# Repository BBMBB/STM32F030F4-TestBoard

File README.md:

# STM32F030F4-TestBoard

## Summary

Simple breadbord compatible testboard based on the STM32F030F4.
I created this pcb to test various applications with the STM32F030F4.
The SWD-Port is accessable through a seperate pinheader for programming.

## Screenshots

## BOM

| **Designator** | **Quantity** | **Value**   | **LCSC** |
|----------------|--------------|-------------|----------|
| C1, C2         | 2            | 10 uF       | C72487   |
| C7, C8, C11    | 3            | 100 nF      | C110253  |
| C9, C10        | 2            | 1 uF        | C1848    |
| R5             | 1            | 0 Ohm       | C100045  |
| U1             | 1            | LM1117-3.3  | C126027  |
| U2             | 1            | STM32F030F4 | C89040   |

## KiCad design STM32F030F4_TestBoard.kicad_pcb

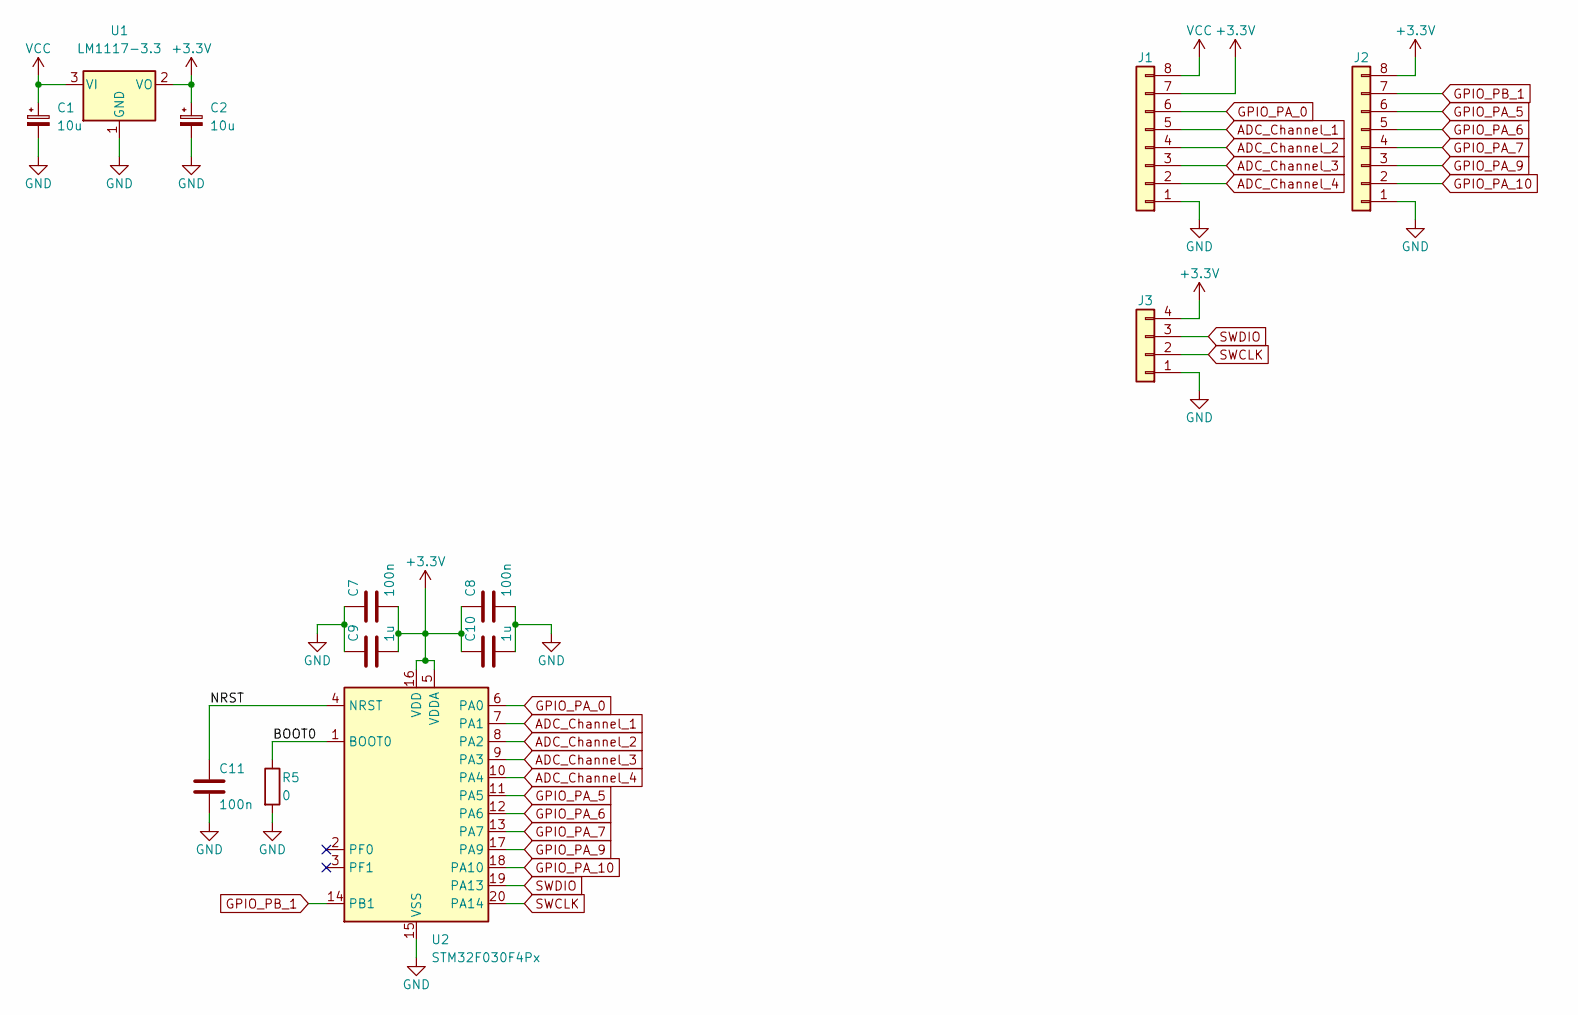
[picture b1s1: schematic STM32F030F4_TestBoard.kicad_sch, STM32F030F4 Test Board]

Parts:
C1, C2: 10u; CP_Elec_5x5.4; LCSC C72487
C7, C8, C11: 100n; C_1206_3216Metric; LCSC C110253
C9, C10: 1u; C_1206_3216Metric; LCSC C1848
J1, J2: Conn_01x08; PinHeader_1x08_P2.54mm_Vertical
J3: Conn_01x04; PinHeader_1x04_P2.54mm_Vertical
R5: 0; R_0805_2012Metric; LCSC C100045
U1: LM1117-3.3; SOT-223-3_TabPin2; LCSC C126027
U2: STM32F030F4Px; TSSOP-20_4.4x6.5mm_P0.65mm

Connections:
+3V3: C2.1, C7.2, C8.1, C9.2, C10.1, J1.7, J2.8, J3.4, U1.2 (VO), U2.5 (VDDA), U2.16 (VDD)
/BOOT0: R5.1, U2.1 (BOOT0)
/NRST: C11.1, U2.4 (NRST)
ADC_Channel_1: J1.5, U2.7 (PA1)
ADC_Channel_2: J1.4, U2.8 (PA2)
ADC_Channel_3: J1.3, U2.9 (PA3)
ADC_Channel_4: J1.2, U2.10 (PA4)
GND: C1.2, C2.2, C7.1, C8.2, C9.1, C10.2, C11.2, J1.1, J2.1, J3.1, R5.2, U1.1 (GND), U2.15 (VSS)
GPIO_PA_0: J1.6, U2.6 (PA0)
GPIO_PA_5: J2.6, U2.11 (PA5)
GPIO_PA_6: J2.5, U2.12 (PA6)
GPIO_PA_7: J2.4, U2.13 (PA7)
GPIO_PA_9: J2.3, U2.17 (PA9)
GPIO_PA_10: J2.2, U2.18 (PA10)
GPIO_PB_1: J2.7, U2.14 (PB1)
SWCLK: J3.2, U2.20 (PA14)
SWDIO: J3.3, U2.19 (PA13)
VCC: C1.1, J1.8, U1.3 (VI)

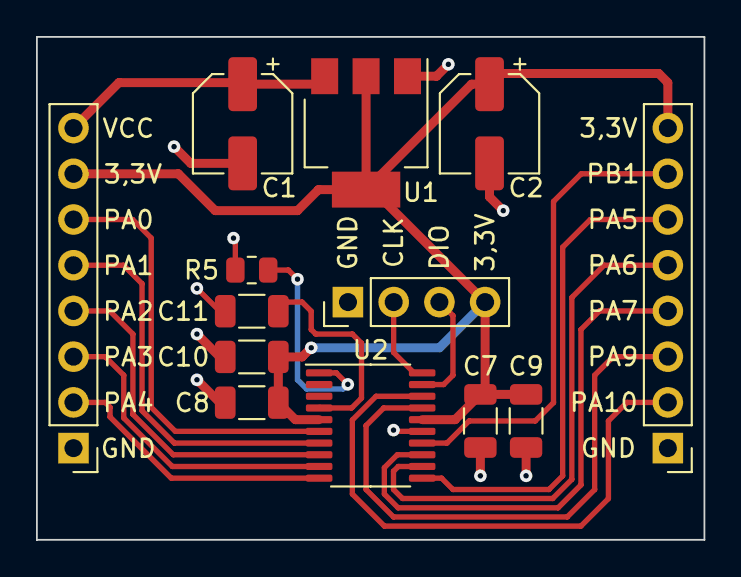
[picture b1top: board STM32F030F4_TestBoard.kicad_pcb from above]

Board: 2 copper layers, 37.1 x 27.9 mm, 13 parts (0 on the bottom side), 18 nets.

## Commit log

2022-07-31 Update .gitignore
    Updated .gitignore to ignore Output folder for gerber output files
2022-07-31 Added Hardware Rev. 0.1
    Added KiCAD Project for Hardware Rev. 0.1
2022-08-09 Added Screenshots
